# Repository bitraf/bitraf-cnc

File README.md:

# Bitraf-cnc
CNC-related research and projects at Bitraf

 config/	configuration for our machines

 docs/		documentation

 docs/shopbot	document Shopbot specifics
 
 [Hrbl-shopbot edition a new arduino and GRBL powered controller card for the bitraf shopbot](Hrbl-shield_readme.md)
 
 [Please contribute by discussing the open Issues!](https://github.com/bitraf/bitraf-cnc/issues)

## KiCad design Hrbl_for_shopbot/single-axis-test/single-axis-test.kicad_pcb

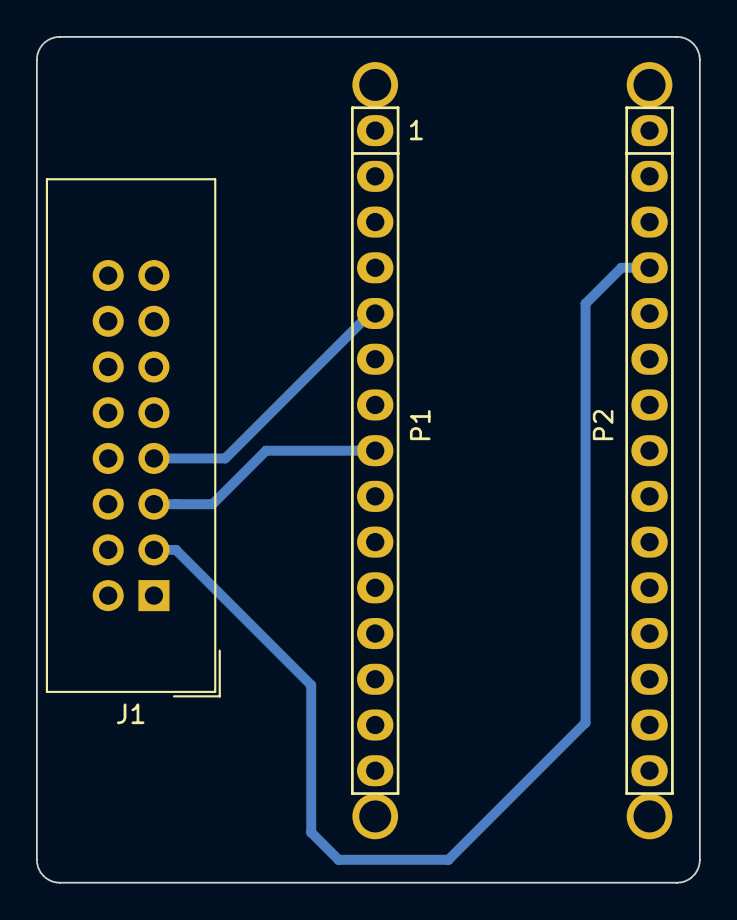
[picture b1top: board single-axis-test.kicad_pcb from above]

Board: 2 copper layers, 36.8 x 47.0 mm, 7 parts (0 on the bottom side), 4 nets.

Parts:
J1: Conn_02x08_Odd_Even; IDC-Header_2x08_Pitch2.54mm_Straight
P1: Digital; Socket_Strip_Arduino_1x15
P2: Analog; Socket_Strip_Arduino_1x15
P3, P4, P5, P6: CONN_01X01; 1pin_Nano

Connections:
+5V: J1.3, P2.4
/DIR: J1.5, P1.8
/STEP: J1.7, P1.5
GND: J1.1, J1.2, J1.4, J1.6, J1.8, J1.10, J1.12, J1.14, P1.4, P2.2

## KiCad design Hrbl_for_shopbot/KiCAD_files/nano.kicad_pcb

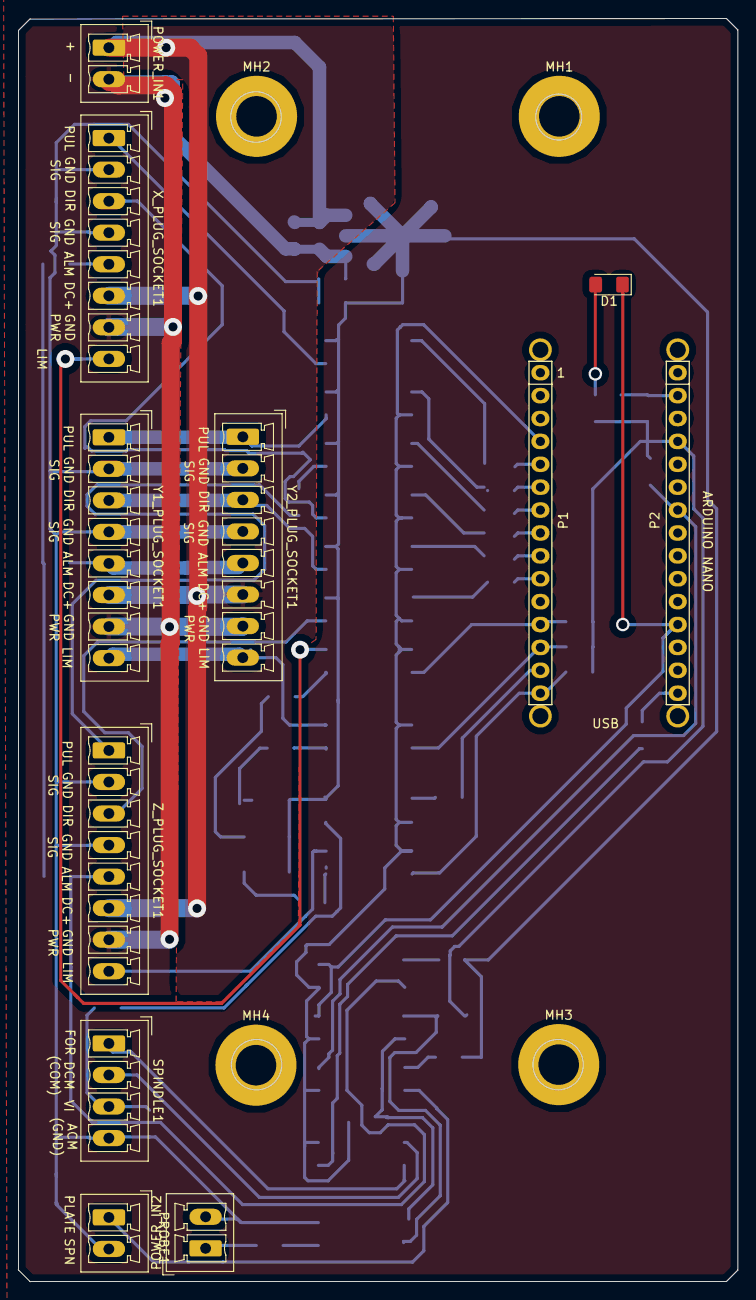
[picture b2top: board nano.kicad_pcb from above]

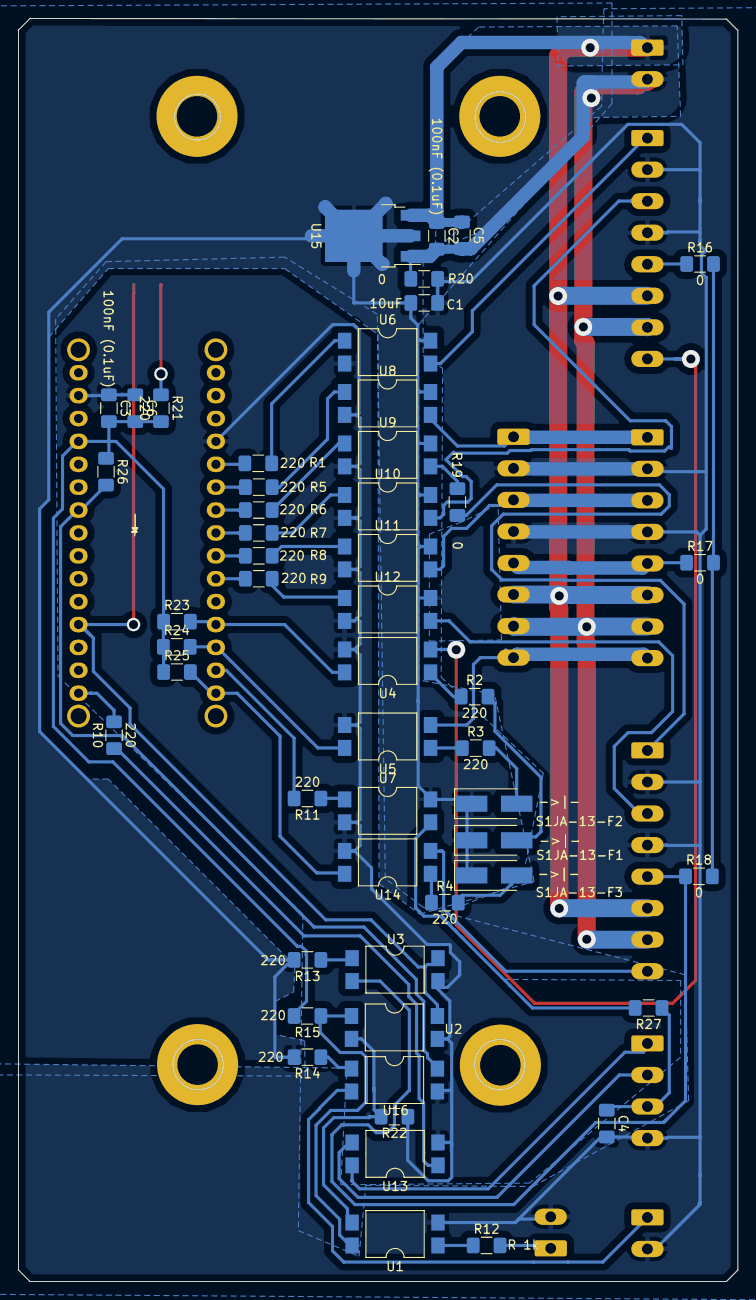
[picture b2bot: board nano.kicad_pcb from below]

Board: 2 copper layers, 79.8 x 140.1 mm, 71 parts (52 on the bottom side), 56 nets.

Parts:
C1, C4, C5, C6: 10uF; C_1206_3216Metric_Pad1.42x1.75mm_HandSolder
C2, C3: 100nF (0.1uF); C_1206_3216Metric_Pad1.42x1.75mm_HandSolder
D1: LED; LED_1206_3216Metric_Pad1.42x1.75mm_HandSolder
MH1, MH2, MH3, MH4: MountingHole; MountingHole_4.5mm_Pad
P1: Digital; Socket_Strip_Arduino_1x15
P2: Analog; Socket_Strip_Arduino_1x15
P3, P4, P5, P6: CONN_01X01; 1pin_Nano
POWER_IN1, POWER_IN2: Conn_01x02; PhoenixContact_MCV_1,5_2-G-3.5_1x02_P3.50mm_Vertical
PROBE1: Conn_01x02; PhoenixContact_MCV_1,5_2-G-3.5_1x02_P3.50mm_Vertical
R1, R2, R3, R4, R5, R6, R7, R8, R9, R10, R11, R13, R14, R15, R21: 220; R_1206_3216Metric_Pad1.42x1.75mm_HandSolder
R12, R27: R 1k; R_1206_3216Metric_Pad1.42x1.75mm_HandSolder
R16, R17, R18, R19, R20, R22: 0; R_1206_3216Metric_Pad1.42x1.75mm_HandSolder
R23, R24, R25, R26: 1000; R_1206_3216Metric_Pad1.42x1.75mm_HandSolder
S1JA-13-F1, S1JA-13-F2, S1JA-13-F3: DIODE; D_SMA_Handsoldering
SPINDLE1: Conn_01x04; PhoenixContact_MCV_1,5_4-G-3.5_1x04_P3.50mm_Vertical
U1, U2, U3, U4, U5, U6, U7, U8, U9, U10, U11, U12, U13, U14, U16: SFH6206-3T; SMDIP-4_W9.53mm_Clearance8mm
U15: IFX27001TFV50ATMA1CT-ND; TO-252-3_TabPin2
X_PLUG_SOCKET1: Conn_01x08; PhoenixContact_MCV_1,5_8-G-3.5_1x08_P3.50mm_Vertical
Y1_PLUG_SOCKET1, Y2_PLUG_SOCKET1: Conn_01x08; PhoenixContact_MCV_1,5_8-G-3.5_1x08_P3.50mm_Vertical
Z_PLUG_SOCKET1: Conn_01x08; PhoenixContact_MCV_1,5_8-G-3.5_1x08_P3.50mm_Vertical

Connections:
5V_ISO: C1.1, R13.2, R14.2, S1JA-13-F1.1, S1JA-13-F2.1, S1JA-13-F3.1, U6.4, U7.4, U8.4, U9.4, U10.4, U11.4, U12.4, U15.2
24V_CONTACTOR_SIGNAL: POWER_IN2.1, R12.2
+5V: C3.2, C6.2, P2.4, R15.2, R21.2, R23.1, R24.1, R25.1, R26.1
+36V: C2.1, C5.1, POWER_IN1.1, U15.3, X_PLUG_SOCKET1.6, Y1_PLUG_SOCKET1.6, Y2_PLUG_SOCKET1.6, Z_PLUG_SOCKET1.6
/DCM(COM): SPINDLE1.2, U13.3
/FOR: SPINDLE1.1, U13.4
/PROBE_PLATE: PROBE1.1, U16.2
/Reset: P1.3, P2.3
/VI: R27.2, U7.3
ABORT: D1.1, P2.12, U2.4, U3.4
ALARM_IN: R16.1, R16.2, R17.1, R17.2, R18.1, R18.2, U3.2, X_PLUG_SOCKET1.5, Y1_PLUG_SOCKET1.5, Y2_PLUG_SOCKET1.5, Z_PLUG_SOCKET1.5
DIR_X: P1.8, R7.2
DIR_X_OUT: U10.3, X_PLUG_SOCKET1.3
DIR_Y: P1.9, R8.2
DIR_Y_OUT: U11.3, Y1_PLUG_SOCKET1.3, Y2_PLUG_SOCKET1.3
DIR_Z: P1.10, R9.2
DIR_Z_OUT: U12.3, Z_PLUG_SOCKET1.3
GND: C3.1, C6.1, P1.4, P2.2, R22.1, R22.2, U1.3, U2.2, U2.3, U3.3, U4.3, U5.3, U6.2, U7.2, U8.2, U9.2, U10.2, U11.2, U12.2, U13.2, U14.3, U16.3
GNDPWR: C2.2, C5.2, POWER_IN1.2, R20.2, U15.1, X_PLUG_SOCKET1.7, Y1_PLUG_SOCKET1.7, Y2_PLUG_SOCKET1.7, Z_PLUG_SOCKET1.7
GNDS: C1.2, C4.2, POWER_IN2.2, PROBE1.2, R20.1, SPINDLE1.4, U1.2, X_PLUG_SOCKET1.2, X_PLUG_SOCKET1.4, Y1_PLUG_SOCKET1.2, Y1_PLUG_SOCKET1.4, Y2_PLUG_SOCKET1.2, Y2_PLUG_SOCKET1.4, Z_PLUG_SOCKET1.2, Z_PLUG_SOCKET1.4
LIM_X: P1.12, R23.2, U4.4
LIM_X_IN: U4.2, X_PLUG_SOCKET1.8
LIM_Y: P1.13, R24.2, U5.4
LIM_Y_IN: U5.2, Y1_PLUG_SOCKET1.8, Y2_PLUG_SOCKET1.8
LIM_Z: P1.15, R25.2, U14.4
LIM_Z_IN: U14.2, Z_PLUG_SOCKET1.8
unnamed: C4.1, R27.1, SPINDLE1.3
unnamed: D1.2, R21.1
unnamed: R1.1, U6.1
unnamed: R2.1, U4.1
unnamed: R2.2, S1JA-13-F1.2
unnamed: R3.1, U5.1
unnamed: R3.2, S1JA-13-F2.2
unnamed: R4.1, U14.1
unnamed: R4.2, S1JA-13-F3.2
unnamed: R5.1, U8.1
unnamed: R6.1, U9.1
unnamed: R7.1, U10.1
unnamed: R8.1, U11.1
unnamed: R9.1, U12.1
unnamed: R10.1, U13.1
unnamed: R11.1, U7.1
unnamed: R12.1, U1.1
unnamed: R13.1, U3.1
unnamed: R14.1, U16.1
unnamed: R15.1, U1.4, U2.1
unnamed: R19.2, U9.3
PROBE: P2.7, R26.2, U16.4
PUL_X: P1.5, R1.2
PUL_X_OUT: U6.3, X_PLUG_SOCKET1.1
PUL_Y: P1.6, R5.2
PUL_Y_OUT: U8.3, Y1_PLUG_SOCKET1.1, Y2_PLUG_SOCKET1.1
PUL_Z: P1.7, R6.2
PUL_Z_OUT: R19.1, Z_PLUG_SOCKET1.1
SPINDLE_EN: P2.15, R10.2
SPINDLE_PWM: P1.14, R11.2

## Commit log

2018-10-11 expeanded readme a bit
2018-10-11 add a docs folder, and a docs/shopbot folder
2018-10-11 Hrbl shield RAW, needs updates for shopbot
2018-10-11 GRBL source code with HRBL settings
2018-10-11 BOM and DXF
2018-10-11 added notes from survey of Bitraf's shopbot
2018-10-11 added images from survey of Bitraf's shopbot
2018-10-11 improved formatting of notes
2018-10-11 added manual for shopbot motor and driver
2018-10-12 pwm smooth circuit
2018-10-12 Updated schematic
2018-10-15 Updated with 24V Contactor signal and PWM filter
2018-10-15 CNC mill ready DXF for single axis board
2018-10-15 kicad project files for single axis board
2018-10-15 added octoprint link
2018-10-16 README - improve formatting
2018-10-19 add a testing directory
2018-10-19 add test report
2018-10-19 add images
2018-10-19 document that videos are too large
2018-10-19 correct link to DXF file
2018-10-22 ShopBot: add wiring diagrams (power, control)
2018-10-22 added images of milling bits used for the test
2018-10-22 added description of milling bits used in the test
2018-10-23 add VCarve project file
2018-10-23 add drill holes toolpath
2018-10-23 add isolation milling toolpath
2018-10-24 Hattori: PCB milling test number 2
2018-10-28 shopbot document on calibrating steps per mm
2018-10-28 udated single axis test board
2018-10-28 udated motor pinout
2018-10-28 tweaked single axis board
2018-10-28 added test report form single axis card
2018-10-28 updated test description and added new pinout
2018-10-28 fixed typos
2018-11-05 Kicad files
2018-11-22 add config subdirectory
2018-11-22 add grbl config for Hattori
2018-11-22 Hattori: add VCarve postprocessor for Hattori
2018-11-23 add VCarve tool library for Hattori
2018-11-23 add probe Z gcode for Hattori (from Jens D. dropbox)
2019-01-30 macros for the small milling machine
2020-04-14 standardBitrafSettings.sbd for Parameter reset
    For when the acceleration values get corrupted. Quoting the wiki:
    "Fikse problemer
    Parameter reset
    Noen ganger virker ikke ShopBot'en og man får feilmeldinger om endestopp selv om spindelen står midt på fresebordet. Da kan det være nødvendig med en parameter reset. Fra ShopBot Control velg
    Utilities
    Reset Settings
